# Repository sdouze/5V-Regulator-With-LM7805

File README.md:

# 5V Regulator using LM7805

I built this because I wanted to power a 5V Fan using 12V power supply.
It is a simple circuit but I decided to make schematic and design a PCB for practice.

From this project I learned how to use a LM7805 voltage regulator and also practiced schematic and pcb design in KiCad

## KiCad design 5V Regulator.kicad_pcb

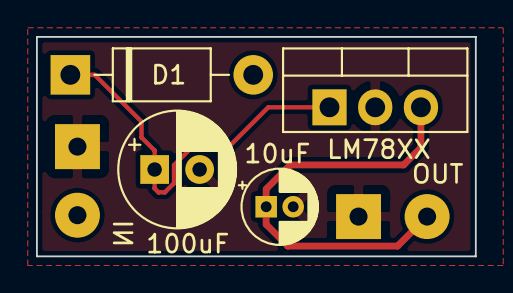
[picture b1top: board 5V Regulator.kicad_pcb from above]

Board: 2 copper layers, 24.4 x 12.2 mm, 6 parts (0 on the bottom side), 4 nets.

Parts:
10uF: 10μF; CP_Radial_D4.0mm_P1.50mm
100uF: 100μF; CP_Radial_D6.3mm_P2.50mm
D1: 1N4002; D_DO-41_SOD81_P10.16mm_Horizontal
IN: Input; SolderWirePad_1x02_P3.81mm_Drill1mm
LM78XX: LM7805_TO220; TO-220-3_Vertical
OUT: Output; SolderWirePad_1x02_P3.81mm_Drill1mm

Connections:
+5V: 10uF.1, LM78XX.3, OUT.2
Earth: 10uF.2, 100uF.2, IN.1, LM78XX.2, OUT.1
unnamed: 100uF.1, D1.1, LM78XX.1
VCC: D1.2, IN.2

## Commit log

2020-02-24 Schematic and KiCad Project
2020-02-24 readme
2020-02-24 update schematic and commit pcb and netlist
